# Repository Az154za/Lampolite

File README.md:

# Lampolite
Lampolite is a lamp that runs when interacting with the touchpad for about 5.2 seconds 
# BOM ( Bill of material )
- 2 ICC timer NE555P
- 1 One expansion GIO pins 4017
- 20 LEDs
- 4 resistors
- 1 variable resistor
- 4 capacitors ( one is polarized )
- 6 pin headers : 3 for powering up the circuit and 3 for the TTP223 sensor
- The TTP223 Sensor
# PCB and schematics 
Here is the schematic 

Here is the PCB :

Here is the 3D overview of the PCB:

 This is the project build :

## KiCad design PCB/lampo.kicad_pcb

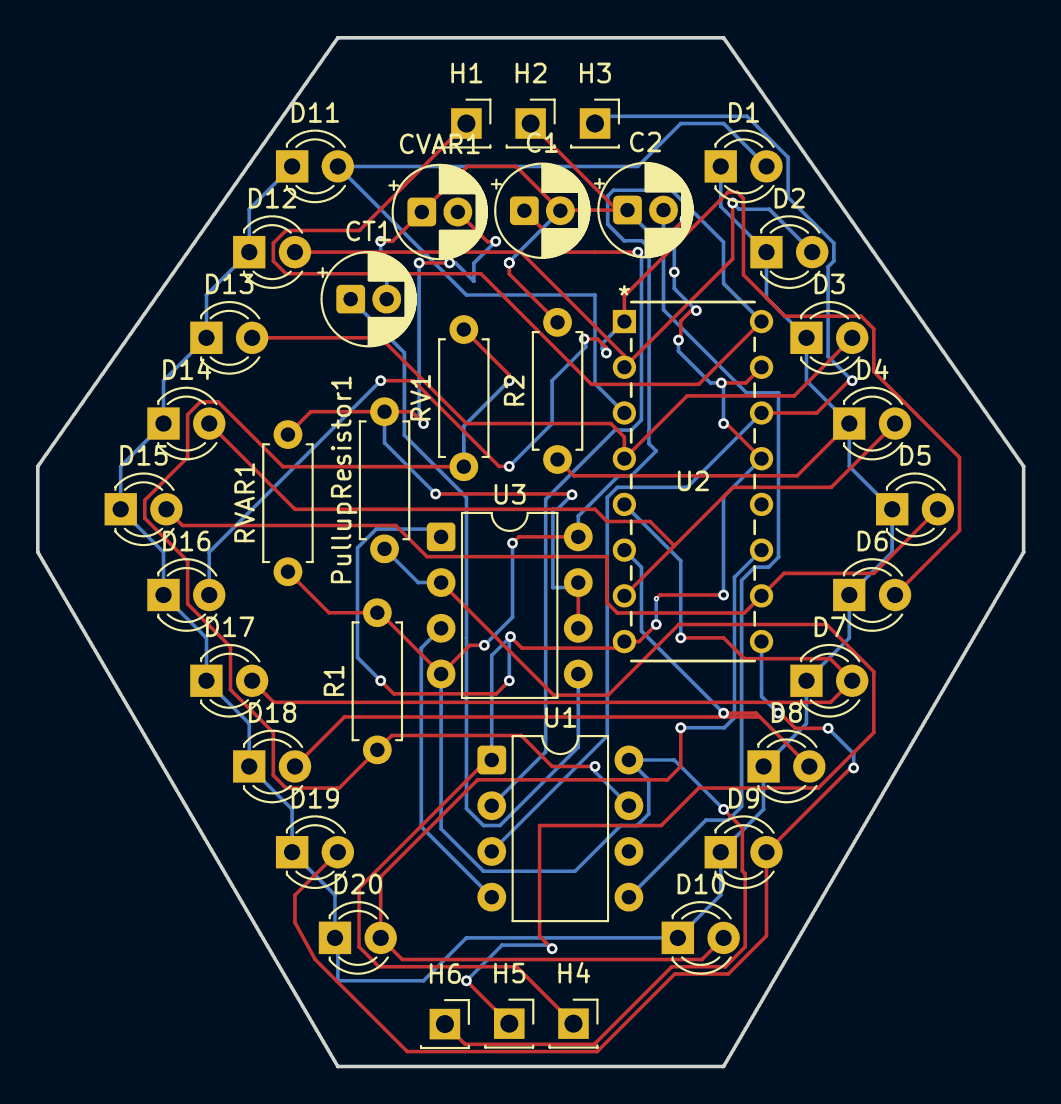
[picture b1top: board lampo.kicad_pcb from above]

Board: 2 copper layers, 54.8 x 57.1 mm, 38 parts (0 on the bottom side), 21 nets.

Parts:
C1: 1 uf; CP_Radial_D5.0mm_P2.00mm
C2: 0.01uF; CP_Radial_D5.0mm_P2.00mm
CT1: 10nF; CP_Radial_D5.0mm_P2.00mm
CVAR1: 10uF; CP_Radial_D5.0mm_P2.00mm
D1, D2, D3, D4, D5, D6, D7, D8, D9, D10, D11, D12, D13, D14, D15, D16, D17, D18, D19, D20: LED; LED_D3.0mm
H1, H2, H3, H4, H5, H6: PinSocket_1x01_P2.54mm_Vertical
PullupResistor1: 10k; R_Axial_DIN0207_L6.3mm_D2.5mm_P7.62mm_Horizontal
R1: 1k; R_Axial_DIN0207_L6.3mm_D2.5mm_P7.62mm_Horizontal
R2: 470; R_Axial_DIN0207_L6.3mm_D2.5mm_P7.62mm_Horizontal
RV1: 50k; R_Axial_DIN0207_L6.3mm_D2.5mm_P7.62mm_Horizontal
RVAR1: 500k; R_Axial_DIN0207_L6.3mm_D2.5mm_P7.62mm_Horizontal
U1, U3: NE555P; DIP-8_W7.62mm
U2: 4017; N16

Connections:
+5V: H1.1, H6.1, R1.2, RVAR1.1, U1.8 (VCC), U2.16 (VDD), U3.4 (R), U3.8 (VCC)
GND: C1.2, C2.1, CT1.2, CVAR1.1, H2.1, H4.1, R2.2, U1.1 (GND), U2.8 (VSS), U2.13 (CKEN), U2.15 (Reset), U3.1 (GND)
L1: D1.2 (A), D11.2 (A), U2.3 (Q0)
L2: D2.2 (A), D12.2 (A), U2.2 (Q1)
L3: D3.2 (A), D13.2 (A), U2.4 (Q2)
L4: D4.2 (A), D14.2 (A), U2.7 (Q3)
L5: D5.2 (A), D15.2 (A), U2.10 (Q4)
L6: D6.2 (A), D16.2 (A), U2.1 (Q5)
L7: D7.2 (A), D17.2 (A), U2.5 (Q6)
L8: D8.2 (A), D18.2 (A), U2.6 (Q7)
L9: D9.2 (A), D19.2 (A), U2.9 (Q8)
L10: D10.2 (A), D20.2 (A), U2.11 (Q9)
unnamed: D1.1 (K), D2.1 (K), D3.1 (K), D4.1 (K), D5.1 (K), D6.1 (K), D7.1 (K), D8.1 (K), D9.1 (K), D10.1 (K), D11.1 (K), D12.1 (K), D13.1 (K), D14.1 (K), D15.1 (K), D16.1 (K), D17.1 (K), D18.1 (K), D19.1 (K), D20.1 (K), R2.1
unnamed: C2.2, U1.5 (CV)
unnamed: R1.1, RV1.1, RV1.2, U1.7 (DIS)
unnamed: C1.1, U1.2 (TR)
unnamed: CT1.1, U3.5 (CV)
unnamed: CVAR1.2, PullupResistor1.2, RVAR1.2, U3.6 (THR), U3.7 (DIS)
unnamed: H5.1, PullupResistor1.1, U3.2 (TR)
OUT: H3.1, U1.3 (Q), U2.14 (CLK)
OUTPUT: U1.4 (R), U3.3 (Q)

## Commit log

2025-12-17 Update README with schematic and PCB images
    Added images for schematic, PCB, and 3D overview.
2025-12-27 Revise BOM.csv with new prices and totals
    Updated component prices and total costs in BOM.
2026-01-22 Update README with project build image
    Added a new image and project build section to the README.
2026-01-22 Update README with additional spacing
    Add spacing and formatting to the README section.
